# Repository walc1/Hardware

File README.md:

# Hardware
Hardware-Projekte der n-tree

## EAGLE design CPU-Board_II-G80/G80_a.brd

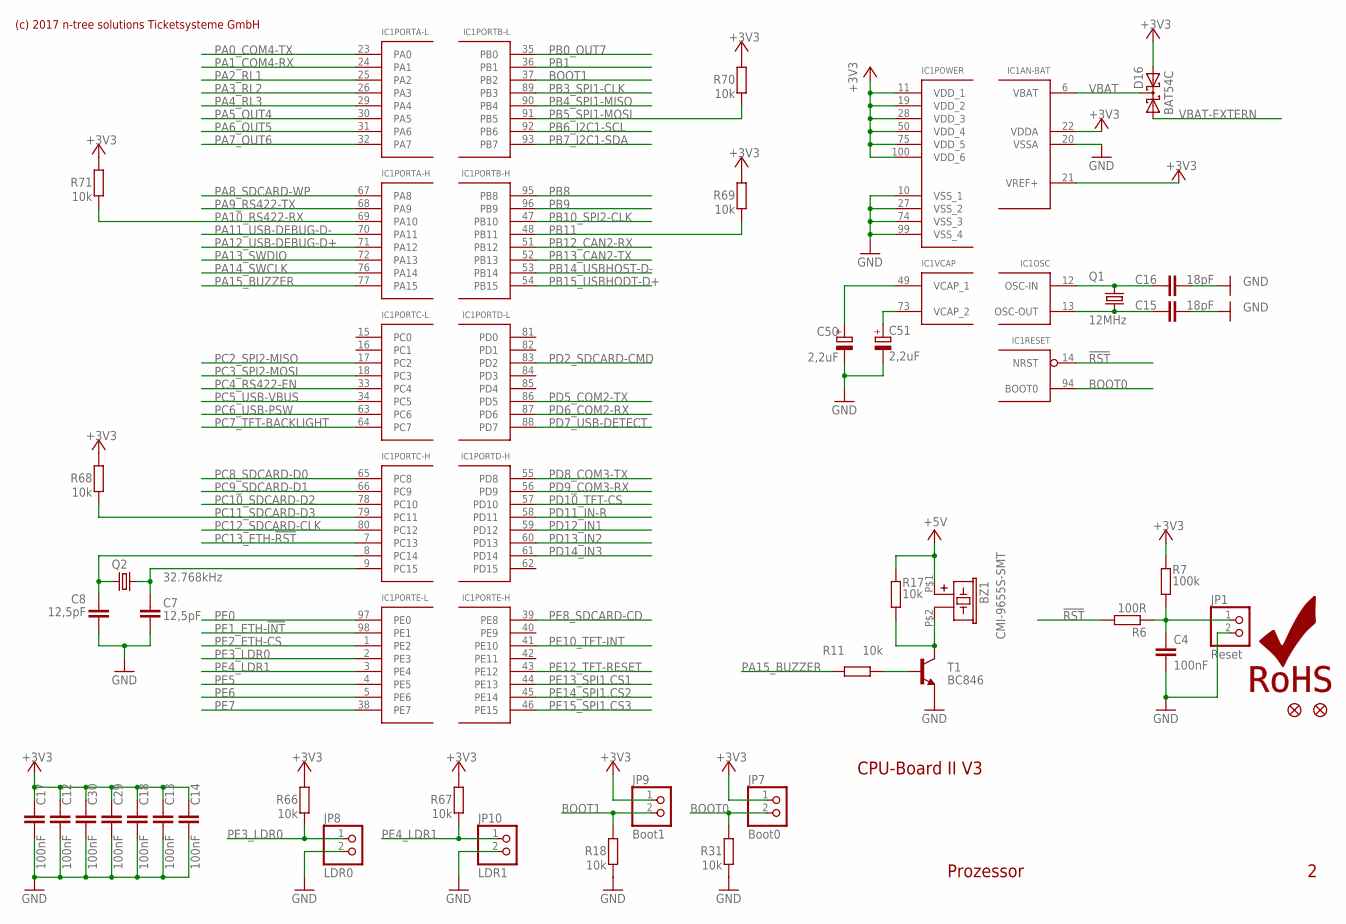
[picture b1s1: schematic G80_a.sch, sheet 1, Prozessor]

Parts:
BZ1: CMI-9655S-SMT; KTG0905CL
C4, C12, C13, C14, C17, C18, C29, C30: 100nF; C0603
C7, C8: 12,5pF; C0603
C15, C16: 18pF; C0603
C50, C51: 2,2uF; CT3216
D16: BAT54C; SOT23
FID1, FID2: FIDUCIAL1X2; FIDUCIAL-1X2
IC1: STM32F107; LQFP100
JP1: Reset; 1X02
JP7: Boot0; 1X02
JP8: LDR0; 1X02
JP9: Boot1; 1X02
JP10: LDR1; 1X02
LOGO1: ROHS_LOGO; ROHS_LOGO_0.18_IN
Q1: 12MHz; CTS406
Q2: 32.768kHz; 3.2X1.5-2-PAD
R6: 100R; R0603
R7: 100k; R0603
R11, R17, R18, R31, R66, R67, R68, R69, R70, R71: 10k; R0603
T1: BC846; SOT23

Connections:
!RST: IC1.14 (NRST), R6.2; also elsewhere on the board
+3V3: C12.1, C13.1, C14.1, C17.1, C18.1, C29.1, C30.1, D16.2 (A2), IC1.11 (VDD_1), IC1.19 (VDD_2), IC1.21 (VREF+), IC1.22 (VDDA), IC1.28 (VDD_3), IC1.50 (VDD_4), IC1.75 (VDD_5), IC1.100 (VDD_6), JP7.1, JP9.1, R7.2, R66.1, R67.1, R68.1, R69.1, R70.1, R71.1; also elsewhere on the board
+5V: BZ1.P$1 (1), R17.1; also elsewhere on the board
BOOT0: IC1.94 (BOOT0), JP7.2, R31.1
BOOT1: IC1.37 (PB2), JP9.2, R18.1
GND: C4.2, C7.2, C8.2, C12.2, C13.2, C14.2, C15.2, C16.2, C17.2, C18.2, C29.2, C30.2, C50.-, C51.-, IC1.10 (VSS_1), IC1.20 (VSSA), IC1.27 (VSS_2), IC1.74 (VSS_3), IC1.99 (VSS_4), JP1.2, JP8.2, JP10.2, R18.2, R31.2, T1.2 (E); also elsewhere on the board
unnamed: C15.1, IC1.13 (OSC-OUT), Q1.1
unnamed: C16.1, IC1.12 (OSC-IN), Q1.3 (2)
unnamed: C7.1, IC1.9 (PC15), Q2.2
unnamed: C8.1, IC1.8 (PC14), Q2.1
unnamed: C51.+, IC1.73 (VCAP_2)
unnamed: BZ1.P$2 (2), R17.2, T1.3 (C)
unnamed: R11.2, T1.1 (B)
unnamed: C4.1, JP1.1, R6.1, R7.1
unnamed: C50.+, IC1.49 (VCAP_1)
PA0_COM4-TX: IC1.23 (PA0); also elsewhere on the board
PA1_COM4-RX: IC1.24 (PA1); also elsewhere on the board
PA2_RL1: IC1.25 (PA2); also elsewhere on the board
PA3_RL2: IC1.26 (PA3); also elsewhere on the board
PA4_RL3: IC1.29 (PA4); also elsewhere on the board
PA5_OUT4: IC1.30 (PA5); also elsewhere on the board
PA6_OUT5: IC1.31 (PA6); also elsewhere on the board
PA7_OUT6: IC1.32 (PA7); also elsewhere on the board
PA8_SDCARD-WP: IC1.67 (PA8)
PA9_RS422-TX: IC1.68 (PA9); also elsewhere on the board
PA10_RS422-RX: IC1.69 (PA10), R71.2; also elsewhere on the board
PA11_USB-DEBUG-D-: IC1.70 (PA11); also elsewhere on the board
PA12_USB-DEBUG-D+: IC1.71 (PA12); also elsewhere on the board
PA13_SWDIO: IC1.72 (PA13); also elsewhere on the board
PA14_SWCLK: IC1.76 (PA14); also elsewhere on the board
PA15_BUZZER: IC1.77 (PA15), R11.1
PB0_OUT7: IC1.35 (PB0); also elsewhere on the board
PB1: IC1.36 (PB1); also elsewhere on the board
PB3_SPI1-CLK: IC1.89 (PB3); also elsewhere on the board
PB4_SPI1-MISO: IC1.90 (PB4); also elsewhere on the board
PB5_SPI1-MOSI: IC1.91 (PB5), R70.2; also elsewhere on the board
PB6_I2C1-SCL: IC1.92 (PB6); also elsewhere on the board
PB7_I2C1-SDA: IC1.93 (PB7); also elsewhere on the board
PB8: IC1.95 (PB8); also elsewhere on the board
PB9: IC1.96 (PB9); also elsewhere on the board
PB10_SPI2-CLK: IC1.47 (PB10); also elsewhere on the board
PB11: IC1.48 (PB11), R69.2; also elsewhere on the board
PB12_CAN2-RX: IC1.51 (PB12); also elsewhere on the board
PB13_CAN2-TX: IC1.52 (PB13); also elsewhere on the board
PB14_USBHOST-D-: IC1.53 (PB14); also elsewhere on the board
PB15_USBHODT-D+: IC1.54 (PB15); also elsewhere on the board
PC2_SPI2-MISO: IC1.17 (PC2); also elsewhere on the board
PC3_SPI2-MOSI: IC1.18 (PC3); also elsewhere on the board
PC4_RS422-EN: IC1.33 (PC4); also elsewhere on the board
PC5_USB-VBUS: IC1.34 (PC5); also elsewhere on the board
PC6_USB-PSW: IC1.63 (PC6); also elsewhere on the board
PC7_TFT-BACKLIGHT: IC1.64 (PC7); also elsewhere on the board
PC8_SDCARD-D0: IC1.65 (PC8); also elsewhere on the board
PC9_SDCARD-D1: IC1.66 (PC9); also elsewhere on the board
PC10_SDCARD-D2: IC1.78 (PC10); also elsewhere on the board
PC11_SDCARD-D3: IC1.79 (PC11), R68.2; also elsewhere on the board
PC12_SDCARD-CLK: IC1.80 (PC12); also elsewhere on the board
PC13_ETH-!RST: IC1.7 (PC13); also elsewhere on the board
PD2_SDCARD-CMD: IC1.83 (PD2); also elsewhere on the board
PD5_COM2-TX: IC1.86 (PD5); also elsewhere on the board
PD6_COM2-RX: IC1.87 (PD6); also elsewhere on the board
PD7_USB-DETECT: IC1.88 (PD7); also elsewhere on the board
PD8_COM3-TX: IC1.55 (PD8); also elsewhere on the board
PD9_COM3-RX: IC1.56 (PD9); also elsewhere on the board
PD10_TFT-CS: IC1.57 (PD10); also elsewhere on the board
PD11_IN-R: IC1.58 (PD11); also elsewhere on the board
PD12_IN1: IC1.59 (PD12); also elsewhere on the board
PD13_IN2: IC1.60 (PD13); also elsewhere on the board
PD14_IN3: IC1.61 (PD14); also elsewhere on the board
PE0: IC1.97 (PE0); also elsewhere on the board
PE1_ETH-!INT: IC1.98 (PE1); also elsewhere on the board
PE2_ETH-CS: IC1.1 (PE2); also elsewhere on the board
PE3_LDR0: IC1.2 (PE3), JP8.1, R66.2
PE4_LDR1: IC1.3 (PE4), JP10.1, R67.2
PE5: IC1.4 (PE5); also elsewhere on the board
PE6: IC1.5 (PE6); also elsewhere on the board
PE7: IC1.38 (PE7); also elsewhere on the board
PE8_SDCARD-CD: IC1.39 (PE8); also elsewhere on the board
PE10_TFT-INT: IC1.41 (PE10); also elsewhere on the board
PE12_TFT-RESET: IC1.43 (PE12); also elsewhere on the board
PE13_SPI1.CS1: IC1.44 (PE13); also elsewhere on the board
PE14_SPI1.CS2: IC1.45 (PE14); also elsewhere on the board
PE15_SPI1.CS3: IC1.46 (PE15); also elsewhere on the board
VBAT: D16.3 (CC), IC1.6 (VBAT)
VBAT-EXTERN: D16.1 (A1); also elsewhere on the board

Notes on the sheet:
CPU-Board II V3
Prozessor
(c) 2017 n-tree solutions Ticketsysteme GmbH

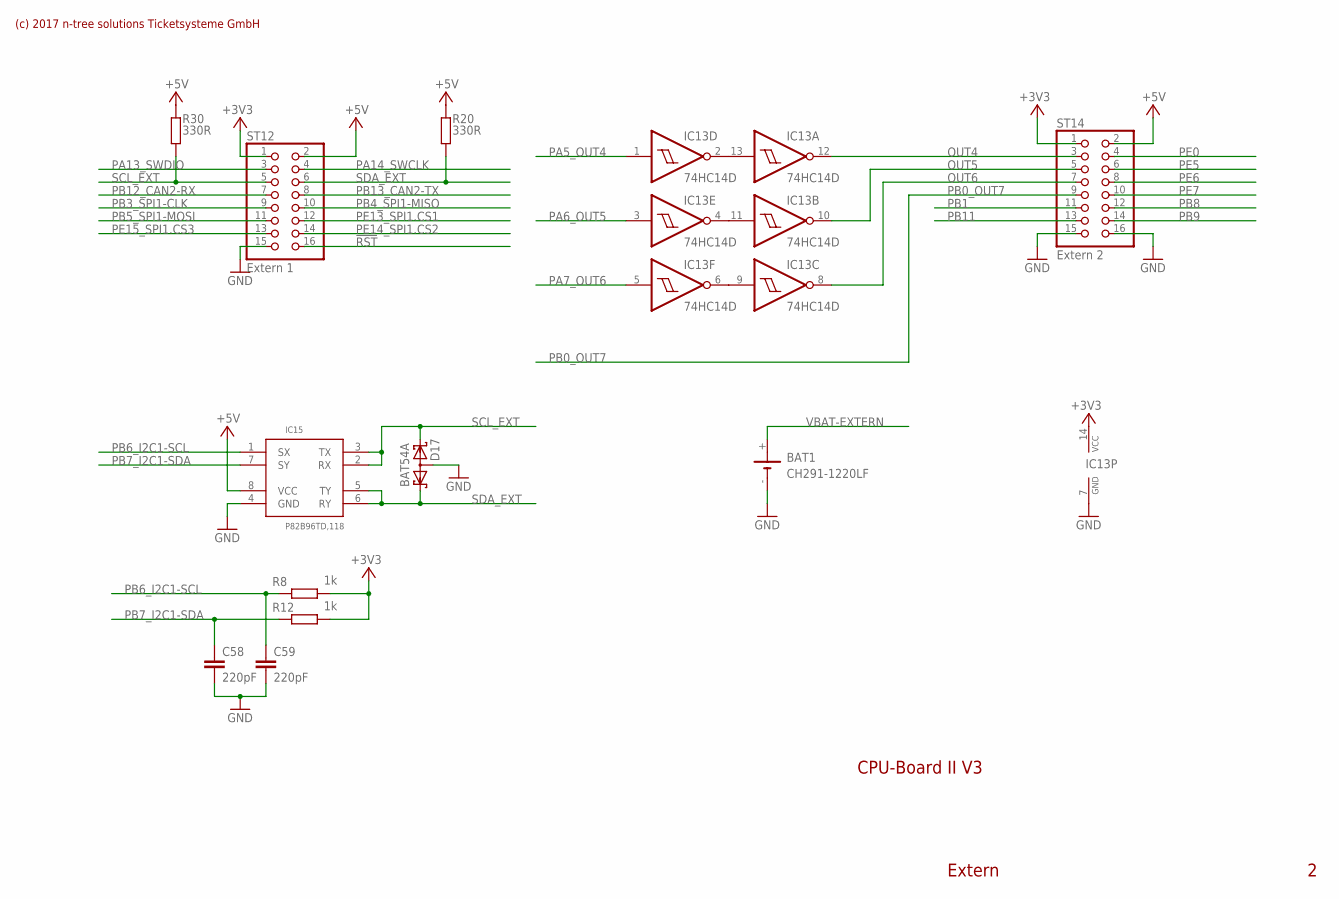
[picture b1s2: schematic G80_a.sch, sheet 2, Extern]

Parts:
BAT1: CH291-1220LF
C58, C59: 220pF; C0603
D17: BAT54A; SOT23
IC13: 74HC14D; SO14
IC15: P82B96TD,118; SO08
R8, R12: 1k; R0603
R20, R30: 330R; R0603
ST12: Extern 1; 2X08
ST14: Extern 2; 2X08

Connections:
!RST: ST12.16; also elsewhere on the board
+3V3: IC13.14 (VCC), R8.2, R12.2, ST12.1, ST14.1; also elsewhere on the board
+5V: IC15.8 (VCC), R20.1, R30.1, ST12.2, ST14.2; also elsewhere on the board
GND: BAT1.-, C58.2, C59.2, D17.3 (AA), IC13.7 (GND), IC15.4 (GND), ST12.15, ST14.15, ST14.16; also elsewhere on the board
unnamed: IC13.2 (O), IC13.13 (I)
unnamed: IC13.4 (O), IC13.11 (I)
unnamed: IC13.6 (O), IC13.9 (I)
OUT4: IC13.12 (O), ST14.3
OUT5: IC13.10 (O), ST14.5
OUT6: IC13.8 (O), ST14.7
PA5_OUT4: IC13.1 (I); also elsewhere on the board
PA6_OUT5: IC13.3 (I); also elsewhere on the board
PA7_OUT6: IC13.5 (I); also elsewhere on the board
PA13_SWDIO: ST12.3; also elsewhere on the board
PA14_SWCLK: ST12.4; also elsewhere on the board
PB0_OUT7: ST14.9; also elsewhere on the board
PB1: ST14.11; also elsewhere on the board
PB3_SPI1-CLK: ST12.9; also elsewhere on the board
PB4_SPI1-MISO: ST12.10; also elsewhere on the board
PB5_SPI1-MOSI: ST12.11; also elsewhere on the board
PB6_I2C1-SCL: C59.1, IC15.1 (SX), R8.1; also elsewhere on the board
PB7_I2C1-SDA: C58.1, IC15.7 (SY), R12.1; also elsewhere on the board
PB8: ST14.12; also elsewhere on the board
PB9: ST14.14; also elsewhere on the board
PB11: ST14.13; also elsewhere on the board
PB12_CAN2-RX: ST12.7; also elsewhere on the board
PB13_CAN2-TX: ST12.8; also elsewhere on the board
PE0: ST14.4; also elsewhere on the board
PE5: ST14.6; also elsewhere on the board
PE6: ST14.8; also elsewhere on the board
PE7: ST14.10; also elsewhere on the board
PE13_SPI1.CS1: ST12.12; also elsewhere on the board
PE14_SPI1.CS2: ST12.14; also elsewhere on the board
PE15_SPI1.CS3: ST12.13; also elsewhere on the board
SCL_EXT: D17.2 (K2), IC15.2 (RX), IC15.3 (TX), R30.2, ST12.5
SDA_EXT: D17.1 (K1), IC15.5 (TY), IC15.6 (RY), R20.2, ST12.6
VBAT-EXTERN: BAT1.+; also elsewhere on the board

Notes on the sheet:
CPU-Board II V3
Extern
(c) 2017 n-tree solutions Ticketsysteme GmbH

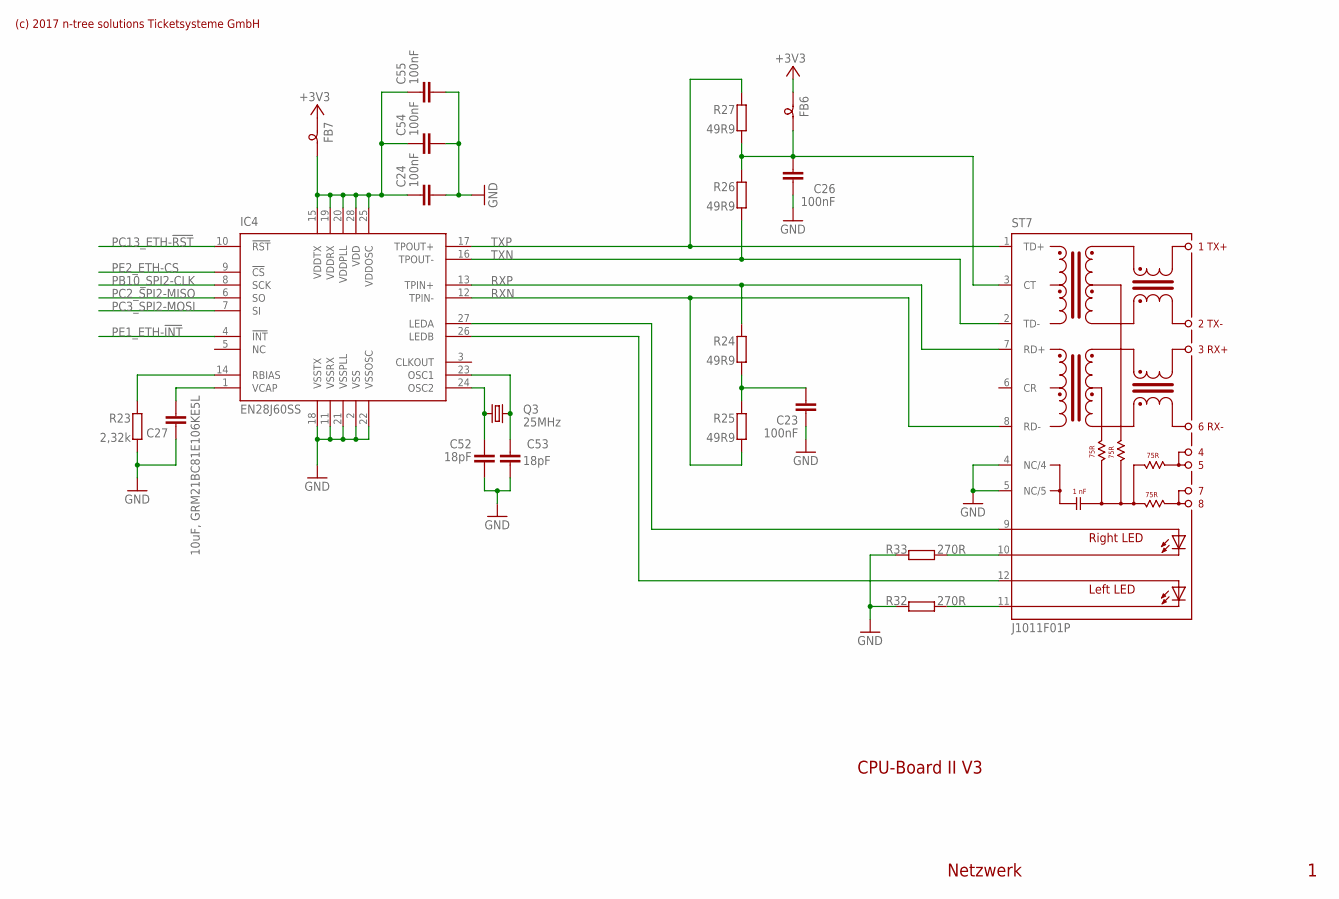
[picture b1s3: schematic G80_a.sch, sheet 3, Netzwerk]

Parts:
C23, C24, C26, C54, C55: 100nF; C0603
C27: 10uF, GRM21BC81E106KE5L; C0805
C52, C53: 18pF; C0603
FB6, FB7: FERITTE-CHIP-BEAD; R805
IC4: EN28J60SS; SSOP28
Q3: 25MHz; CTS406
R23: 2,32k; R0603
R24, R25, R26, R27: 49R9; R0603
R32, R33: 270R; R0603
ST7: J1011F01P; J1

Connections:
+3V3: FB6.1, FB7.1; also elsewhere on the board
GND: C23.2, C24.2, C26.2, C27.2, C52.2, C53.2, C54.2, C55.2, IC4.2 (VSS), IC4.11 (VSSRX), IC4.18 (VSSTX), IC4.21 (VSSPLL), IC4.22 (VSSOSC), R23.1, R32.1, R33.1, ST7.4 (NC/4), ST7.5 (NC/5); also elsewhere on the board
unnamed: R33.2, ST7.10 (C-R)
unnamed: R32.2, ST7.11 (C-L)
unnamed: IC4.27 (LEDA), ST7.9 (A-R)
unnamed: IC4.26 (LEDB), ST7.12 (AL)
unnamed: C24.1, C54.1, C55.1, FB7.2, IC4.15 (VDDTX), IC4.19 (VDDRX), IC4.20 (VDDPLL), IC4.25 (VDDOSC), IC4.28 (VDD)
unnamed: C23.1, R24.1, R25.2
unnamed: C26.1, FB6.2, R26.2, R27.1, ST7.3 (CT)
unnamed: C52.1, IC4.24 (OSC2), Q3.1
unnamed: C53.1, IC4.23 (OSC1), Q3.3 (2)
unnamed: C27.1, IC4.1 (VCAP)
unnamed: IC4.14 (RBIAS), R23.2
PB10_SPI2-CLK: IC4.8 (SCK); also elsewhere on the board
PC2_SPI2-MISO: IC4.6 (SO); also elsewhere on the board
PC3_SPI2-MOSI: IC4.7 (SI); also elsewhere on the board
PC13_ETH-!RST: IC4.10 (!RST); also elsewhere on the board
PE1_ETH-!INT: IC4.4 (!INT); also elsewhere on the board
PE2_ETH-CS: IC4.9 (!CS); also elsewhere on the board
RXN: IC4.12 (TPIN-), R25.1, ST7.8 (RD-)
RXP: IC4.13 (TPIN+), R24.2, ST7.7 (RD+)
TXN: IC4.16 (TPOUT-), R26.1, ST7.2 (TD-)
TXP: IC4.17 (TPOUT+), R27.2, ST7.1 (TD+)

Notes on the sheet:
CPU-Board II V3
Netzwerk
(c) 2017 n-tree solutions Ticketsysteme GmbH

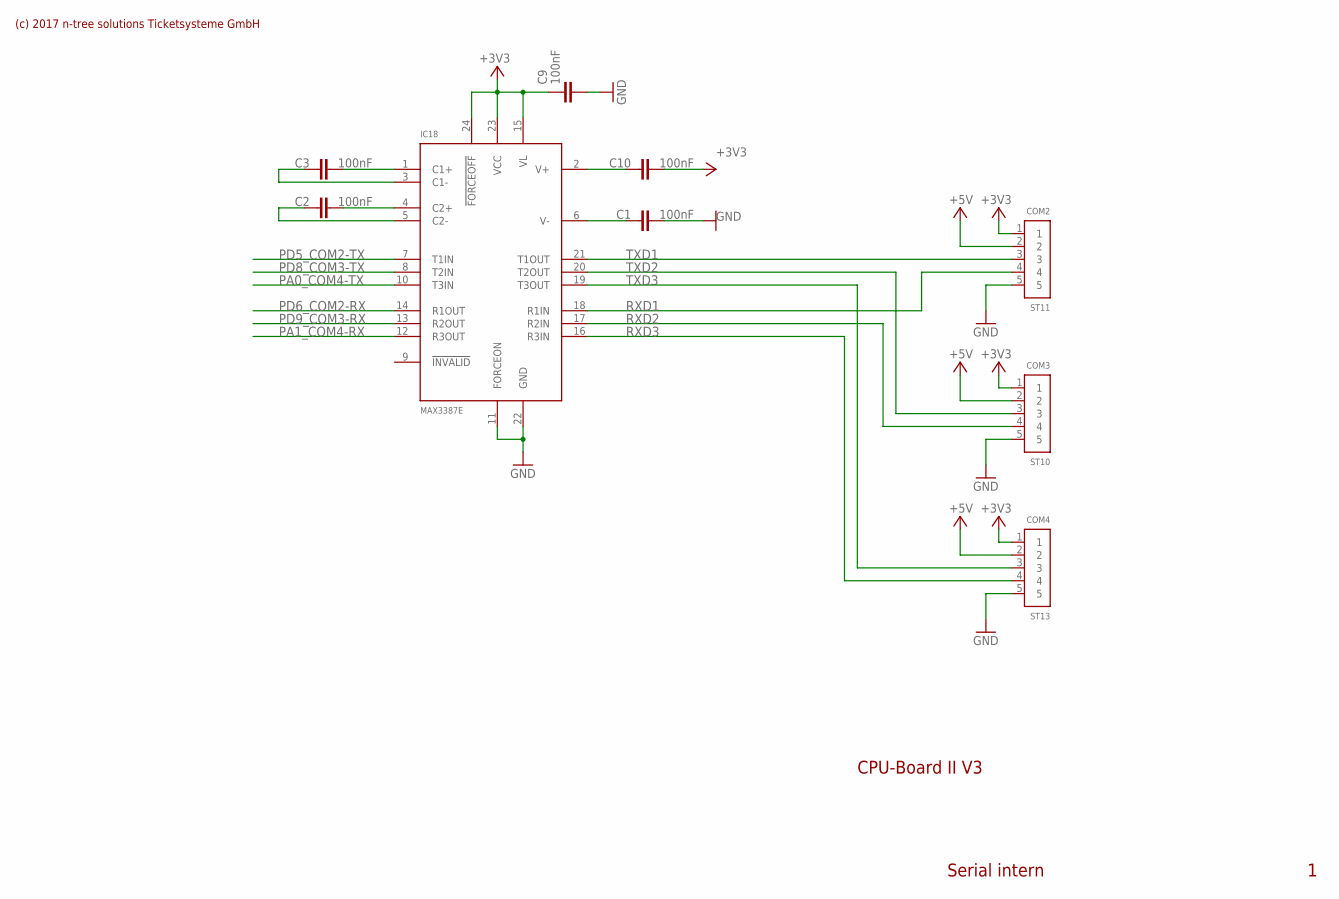
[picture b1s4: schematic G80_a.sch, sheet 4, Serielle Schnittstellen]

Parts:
C1, C2, C3, C9, C10: 100nF; C0603
IC18: MAX3387E; SSOP24
ST10: COM3; JST-EH5
ST11: COM2; JST-EH5
ST13: COM4; JST-EH5

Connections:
+3V3: C9.1, C10.2, IC18.15 (VL), IC18.23 (VCC), IC18.24 (!FORCEOFF), ST10.1, ST11.1, ST13.1; also elsewhere on the board
+5V: ST10.2, ST11.2, ST13.2; also elsewhere on the board
GND: C1.2, C9.2, IC18.11 (FORCEON), IC18.22 (GND), ST10.5, ST11.5, ST13.5; also elsewhere on the board
unnamed: C3.2, IC18.1 (C1+)
unnamed: C3.1, IC18.3 (C1-)
unnamed: C2.2, IC18.4 (C2+)
unnamed: C2.1, IC18.5 (C2-)
unnamed: C10.1, IC18.2 (V+)
unnamed: C1.1, IC18.6 (V-)
PA0_COM4-TX: IC18.10 (T3IN); also elsewhere on the board
PA1_COM4-RX: IC18.12 (R3OUT); also elsewhere on the board
PD5_COM2-TX: IC18.7 (T1IN); also elsewhere on the board
PD6_COM2-RX: IC18.14 (R1OUT); also elsewhere on the board
PD8_COM3-TX: IC18.8 (T2IN); also elsewhere on the board
PD9_COM3-RX: IC18.13 (R2OUT); also elsewhere on the board
RXD1: IC18.18 (R1IN), ST11.4
RXD2: IC18.17 (R2IN), ST10.4
RXD3: IC18.16 (R3IN), ST13.4
TXD1: IC18.21 (T1OUT), ST11.3
TXD2: IC18.20 (T2OUT), ST10.3
TXD3: IC18.19 (T3OUT), ST13.3

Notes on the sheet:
CPU-Board II V3
Serial intern
(c) 2017 n-tree solutions Ticketsysteme GmbH

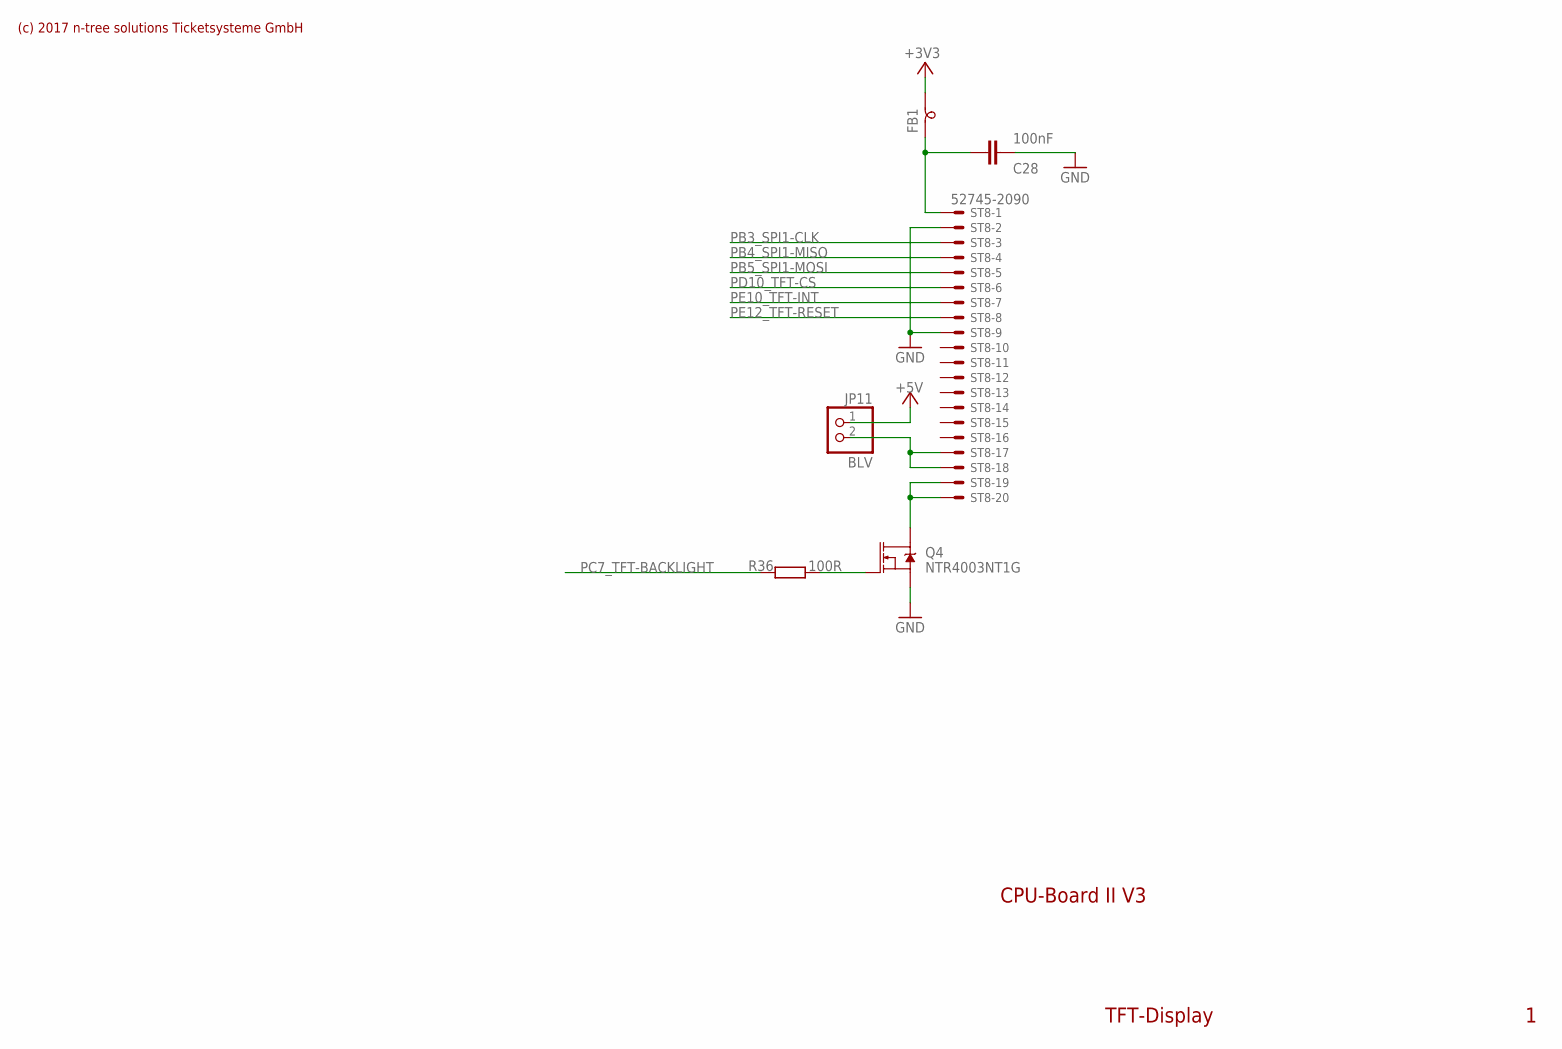
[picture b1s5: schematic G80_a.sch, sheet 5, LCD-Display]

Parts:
C28: 100nF; C0603
FB1: FERITTE-CHIP-BEAD; R805
JP11: BLV; 1X02
Q4: NTR4003NT1G; SOT23-3
R36: 100R; R0603
ST8: 52745-2090

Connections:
+3V3: FB1.2; also elsewhere on the board
+5V: JP11.1; also elsewhere on the board
GND: C28.2, Q4.2 (S), ST8.2, ST8.9; also elsewhere on the board
unnamed: Q4.1 (G), R36.2
unnamed: C28.1, FB1.1, ST8.1
unnamed: Q4.3 (D), ST8.19, ST8.20
unnamed: JP11.2, ST8.17, ST8.18
PB3_SPI1-CLK: ST8.3; also elsewhere on the board
PB4_SPI1-MISO: ST8.4; also elsewhere on the board
PB5_SPI1-MOSI: ST8.5; also elsewhere on the board
PC7_TFT-BACKLIGHT: R36.1; also elsewhere on the board
PD10_TFT-CS: ST8.6; also elsewhere on the board
PE10_TFT-INT: ST8.7; also elsewhere on the board
PE12_TFT-RESET: ST8.8; also elsewhere on the board

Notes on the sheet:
CPU-Board II V3
TFT-Display
(c) 2017 n-tree solutions Ticketsysteme GmbH

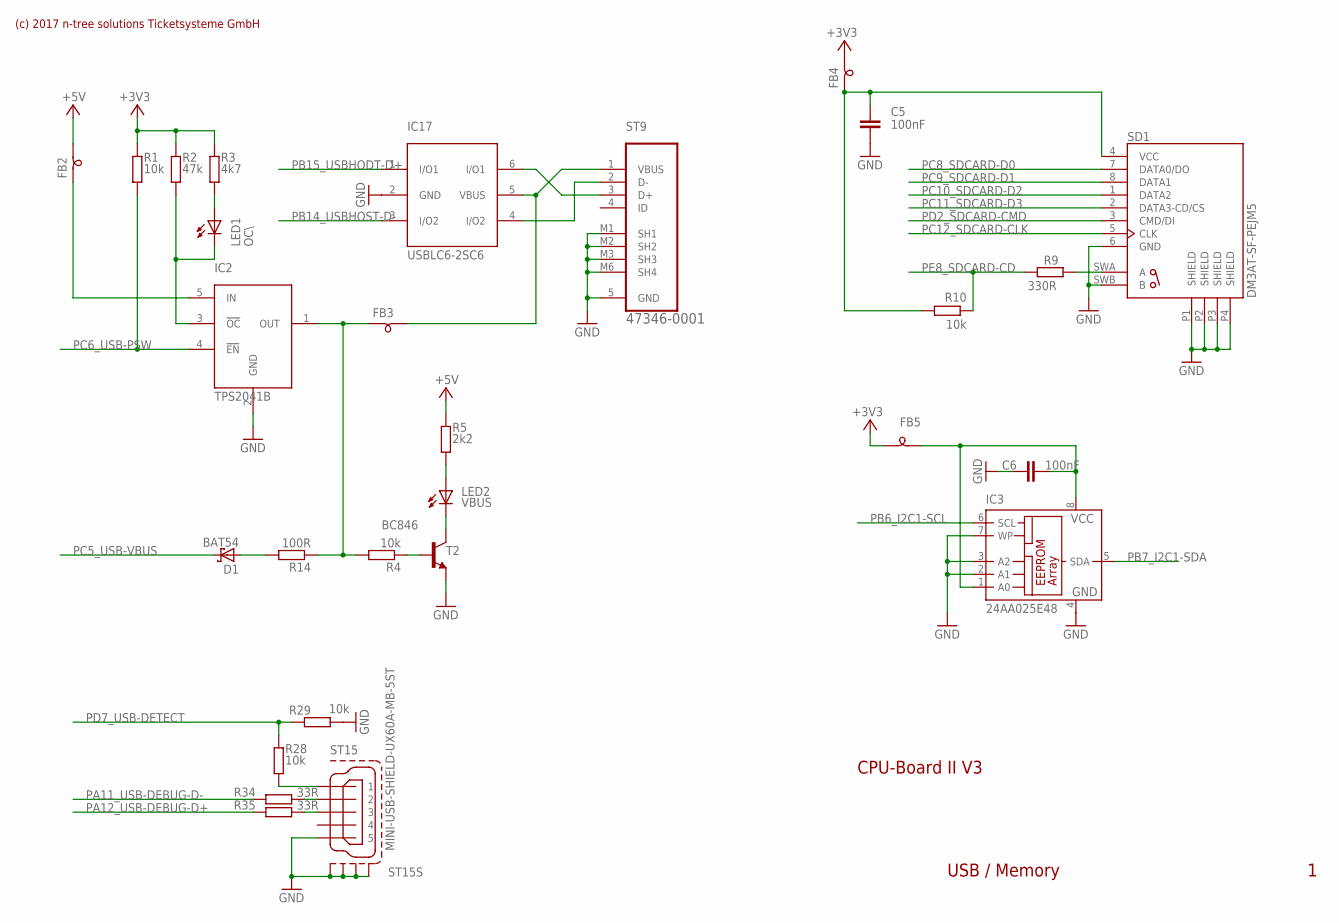
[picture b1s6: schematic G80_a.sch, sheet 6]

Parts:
C5, C6: 100nF; C0603
D1: BAT54; SOT23
FB2, FB3, FB4, FB5: FERITTE-CHIP-BEAD; R805
IC2: TPS2041B; SOT23-5
IC3: 24AA025E48; SO-08M
IC17: USBLC6-2SC6; SO23-6L
LED1: OC\; CHIPLED_0603
LED2: VBUS; CHIPLED_0603
R1, R4, R10, R28, R29: 10k; R0603
R2: 47k; R0603
R3: 4k7; R0603
R5: 2k2; R0603
R9: 330R; R0603
R14: 100R; R0603
R34, R35: 33R; R0603
SD1: DM3AT-SF-PEJM5; HRS_DM3AT-SF-PEJM5
ST9: 47346-0001; MOLEX_47346-0001
ST15: MINI-USB-SHIELD-UX60A-MB-5ST; UX60A-MB-5ST
T2: BC846; SOT23-BEC

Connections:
+3V3: FB4.2, FB5.2, R1.1, R2.1, R3.1; also elsewhere on the board
+5V: FB2.2, R5.1; also elsewhere on the board
GND: C5.2, C6.1, IC2.2 (GND), IC3.2 (A1), IC3.3 (A2), IC3.4 (GND), IC3.7 (WP), IC17.2 (GND), R29.2, SD1.6 (GND), SD1.P1 (SHIELD), SD1.P2 (SHIELD), SD1.P3 (SHIELD), SD1.P4 (SHIELD), SD1.SWB (B), ST9.5 (GND), ST9.M1 (SH1), ST9.M2 (SH2), ST9.M3 (SH3), ST9.M6 (SH4), ST15.5, ST15.M1 (S1), ST15.M2 (S2), ST15.M3 (S3), ST15.M4 (S4), T2.E; also elsewhere on the board
unnamed: LED2.C, T2.C
unnamed: LED1.A, R3.2
unnamed: LED2.A, R5.2
unnamed: R4.1, T2.B
unnamed: FB3.1, IC2.1 (OUT), R4.2, R14.1
unnamed: D1.1 (A), R14.2
unnamed: IC2.3 (!OC), LED1.C, R2.2
unnamed: R9.1, SD1.SWA (A)
unnamed: R28.2, ST15.1
unnamed: R34.1, ST15.2
unnamed: R35.1, ST15.3
unnamed: FB3.2, IC17.5 (VBUS), ST9.1 (VBUS)
unnamed: IC17.6 (I/O1), ST9.3 (D+)
unnamed: FB2.1, IC2.5 (IN)
unnamed: IC17.4 (I/O2), ST9.2 (D-)
unnamed: C5.1, FB4.1, R10.1, SD1.4 (VCC)
unnamed: C6.2, FB5.1, IC3.1 (A0), IC3.8 (VCC)
PA11_USB-DEBUG-D-: R34.2; also elsewhere on the board
PA12_USB-DEBUG-D+: R35.2; also elsewhere on the board
PB6_I2C1-SCL: IC3.6 (SCL); also elsewhere on the board
PB7_I2C1-SDA: IC3.5 (SDA); also elsewhere on the board
PB14_USBHOST-D-: IC17.3 (I/O2); also elsewhere on the board
PB15_USBHODT-D+: IC17.1 (I/O1); also elsewhere on the board
PC5_USB-VBUS: D1.3 (C); also elsewhere on the board
PC6_USB-PSW: IC2.4 (!EN), R1.2; also elsewhere on the board
PC8_SDCARD-D0: SD1.7 (DATA0/DO); also elsewhere on the board
PC9_SDCARD-D1: SD1.8 (DATA1); also elsewhere on the board
PC10_SDCARD-D2: SD1.1 (DATA2); also elsewhere on the board
PC11_SDCARD-D3: SD1.2 (DATA3-CD/CS); also elsewhere on the board
PC12_SDCARD-CLK: SD1.5 (CLK); also elsewhere on the board
PD2_SDCARD-CMD: SD1.3 (CMD/DI); also elsewhere on the board
PD7_USB-DETECT: R28.1, R29.1; also elsewhere on the board
PE8_SDCARD-CD: R9.2, R10.2; also elsewhere on the board

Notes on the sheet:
CPU-Board II V3
USB / Memory
(c) 2017 n-tree solutions Ticketsysteme GmbH

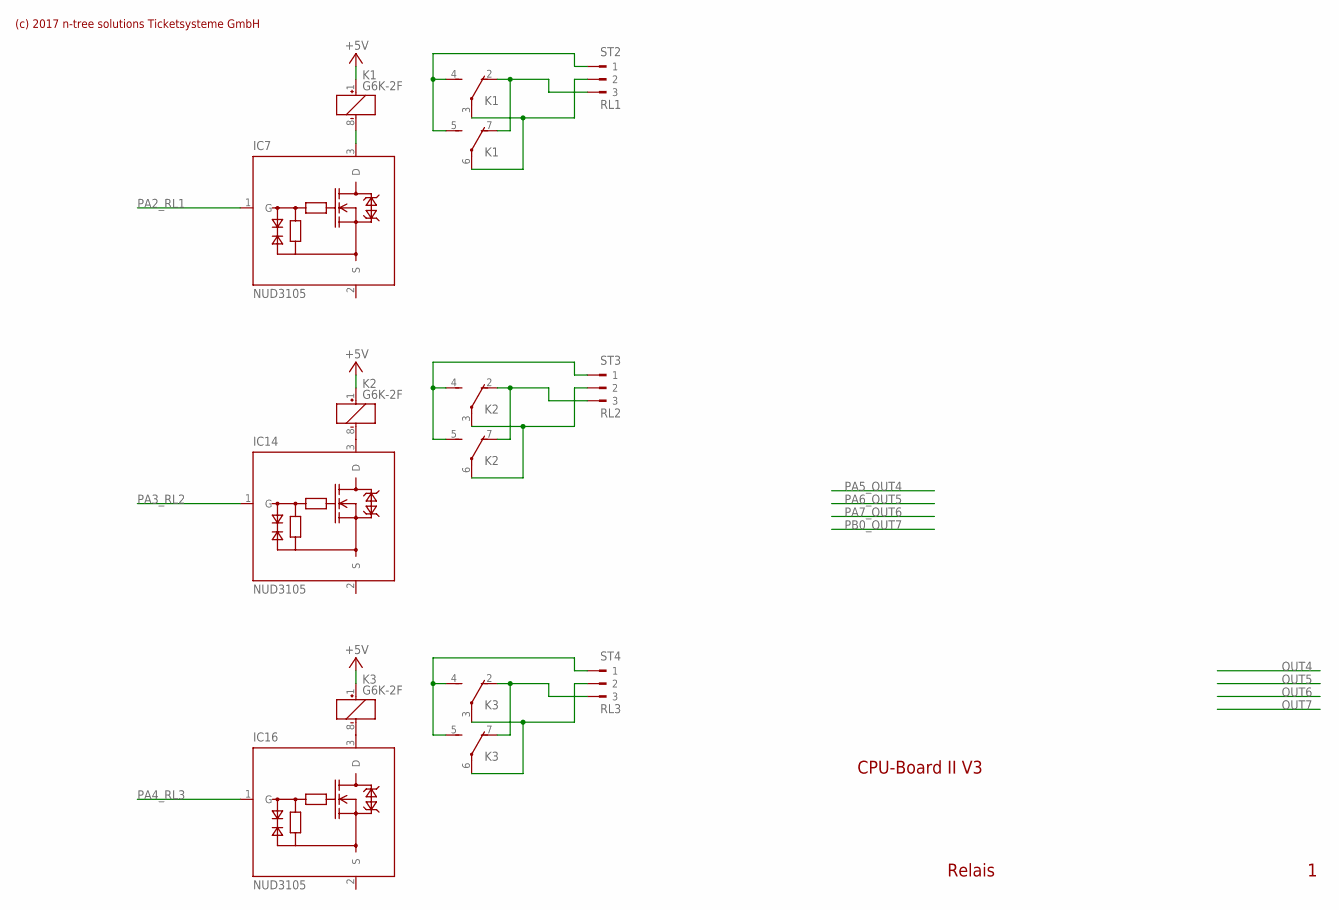
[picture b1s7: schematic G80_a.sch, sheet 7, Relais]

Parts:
IC7, IC14, IC16: NUD3105; SOT23
K1, K2, K3: G6K-2F
ST2: RL1; 180G-3
ST3: RL2; 180G-3
ST4: RL3; 180G-3

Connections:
+5V: K1.1 (+), K2.1 (+), K3.1 (+); also elsewhere on the board
unnamed: K3.4 (S), K3.5 (S), ST4.1
unnamed: K3.2 (O), K3.7 (O), ST4.3
unnamed: K3.3, K3.6, ST4.2
unnamed: K2.4 (S), K2.5 (S), ST3.1
unnamed: K2.2 (O), K2.7 (O), ST3.3
unnamed: K2.3, K2.6, ST3.2
unnamed: K1.4 (S), K1.5 (S), ST2.1
unnamed: K1.2 (O), K1.7 (O), ST2.3
unnamed: K1.3, K1.6, ST2.2
unnamed: IC7.3 (D), K1.8 (-)
unnamed: IC14.3 (D), K2.8 (-)
unnamed: IC16.3 (D), K3.8 (-)
PA2_RL1: IC7.1 (G); also elsewhere on the board
PA3_RL2: IC14.1 (G); also elsewhere on the board
PA4_RL3: IC16.1 (G); also elsewhere on the board

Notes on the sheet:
CPU-Board II V3
(c) 2017 n-tree solutions Ticketsysteme GmbH
Relais

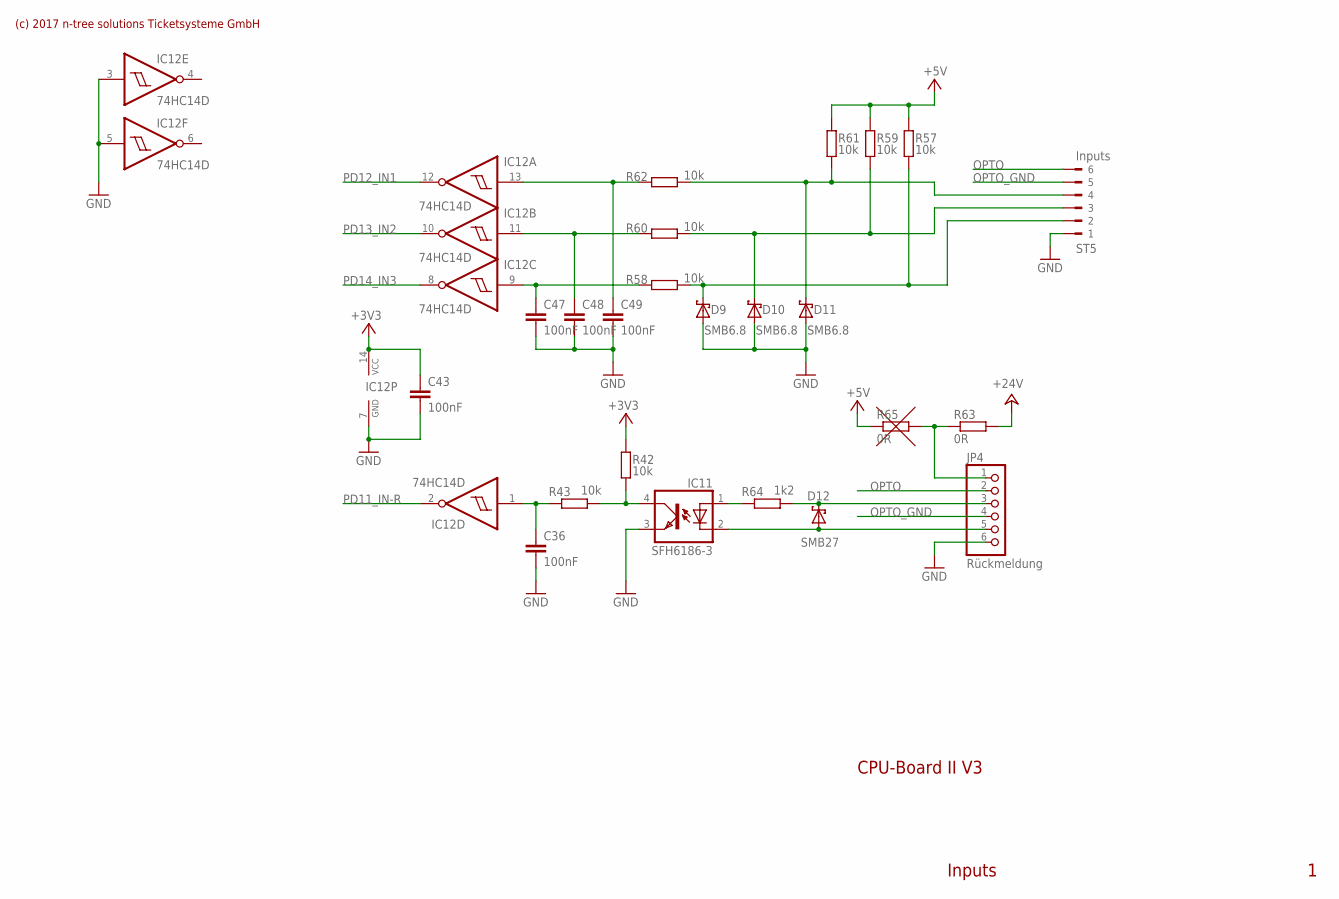
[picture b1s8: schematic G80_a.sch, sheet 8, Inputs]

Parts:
C36, C43, C47, C48, C49: 100nF; C0603
D9, D10, D11: SMB6.8; SMB
D12: SMB27; SMB
IC11: SFH6186-3; SO-6/4
IC12: 74HC14D; SO14
JP4: Rückmeldung; 1X06
R42, R43, R57, R58, R59, R60, R61, R62: 10k; R0603
R63, R65: 0R; R0603
R64: 1k2; R0603
ST5: Inputs; 180G-6

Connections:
+3V3: C43.1, IC12.14 (VCC), R42.2; also elsewhere on the board
+5V: R57.2, R59.2, R61.2, R65.1; also elsewhere on the board
+24V: R63.2; also elsewhere on the board
GND: C36.2, C43.2, C47.2, C48.2, C49.2, D9.A, D10.A, D11.A, IC11.3 (EMIT), IC12.3 (I), IC12.5 (I), IC12.7 (GND), JP4.6, ST5.1; also elsewhere on the board
unnamed: JP4.1, R63.1, R65.2
unnamed: C36.1, IC12.1 (I), R43.1
unnamed: D9.C, R57.1, R58.2, ST5.2
unnamed: D10.C, R59.1, R60.2, ST5.3
unnamed: D11.C, R61.1, R62.2, ST5.4
unnamed: IC11.4 (COL), R42.1, R43.2
unnamed: D12.A, IC11.2 (C), JP4.5
unnamed: D12.C, JP4.3, R64.2
unnamed: IC11.1 (A), R64.1
unnamed: C49.1, IC12.13 (I), R62.1
unnamed: C48.1, IC12.11 (I), R60.1
unnamed: C47.1, IC12.9 (I), R58.1
OPTO: JP4.2, ST5.6
OPTO_GND: JP4.4, ST5.5
PD11_IN-R: IC12.2 (O); also elsewhere on the board
PD12_IN1: IC12.12 (O); also elsewhere on the board
PD13_IN2: IC12.10 (O); also elsewhere on the board
PD14_IN3: IC12.8 (O); also elsewhere on the board

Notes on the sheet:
CPU-Board II V3
(c) 2017 n-tree solutions Ticketsysteme GmbH
Inputs

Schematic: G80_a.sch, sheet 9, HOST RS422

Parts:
C33, C45: 10uF/16V; C/6032-28R
C34, C35, C39, C40, C41, C42, C46: 100nF; C0603
C38: 1uF/16V; A/3216-18R
C44: 10nF/50V; C0603
D3: BZV50C5V6; SOD80C
D4, D5, D6, D8: SMB15A; SMB
D7: BAV99; SOT23
DC1: TME0505S; NME
IC9: TI_SN65HVD3080E
IC10: 74HC14D; SO14
JP2, JP3: RS484Abschluss; 1X02
OK1, OK2, OK3: HCPL0600; SOIC08
R40, R49, R50: 470R; R0603
R41, R47, R48: 1K5; R0603
R51: 10k; R0603
R52, R54, R56: 100R; R0603
R55: 100k; R0603
ST6: HOST; 180G-4

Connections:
+3V3: C35.1, C40.1, C41.1, C42.1, IC10.14 (VCC), OK1.8 (VCC), OK2.2 (A), OK3.2 (A), R41.2; also elsewhere on the board
+5V: C33.+, DC1.2 (+VIN); also elsewhere on the board
GND: C33.-, C35.2, C40.2, C41.2, C42.2, DC1.1 (-VIN), IC10.7 (GND), OK1.5 (GND), R51.1; also elsewhere on the board
GNDIO: C34.2, C38.-, C39.2, C45.-, C46.2, D3.A, D4.2 (A), D5.2 (A), D6.2 (A), D8.2 (A), DC1.3 (-VOUT), IC9.2 (/RE), IC9.5 (GND), OK2.5 (GND), OK3.5 (GND), R52.1
unnamed: IC10.11 (I), IC10.12 (O)
unnamed: IC10.3 (I), IC10.6 (O)
unnamed: OK3.3 (C), R50.2
unnamed: IC10.10 (O), R50.1
unnamed: IC10.1 (I), IC10.8 (O)
unnamed: OK2.3 (C), R49.2
unnamed: IC10.2 (O), R49.1
unnamed: IC9.4 (D), OK2.6 (VO), R47.1
unnamed: IC10.5 (I), OK1.6 (VO), R41.1
unnamed: IC9.1 (R), R40.2
unnamed: JP3.1, R54.2
unnamed: D7.3 (AC), R55.2
unnamed: OK1.3 (C), R40.1
unnamed: IC9.3 (DE), OK3.6 (VO), R48.1
unnamed: C44.1, JP2.1
unnamed: C44.2, R56.2
PA9_RS422-TX: IC10.9 (I); also elsewhere on the board
PA10_RS422-RX: IC10.4 (O); also elsewhere on the board
PC4_RS422-EN: IC10.13 (I), R51.2; also elsewhere on the board
RX+: D6.1 (C), IC9.9 (A), JP2.2, R55.1, ST6.3
RX-: D8.1 (C), IC9.8 (B), R52.2, R56.1, ST6.4
TX+: D4.1 (C), IC9.6 (Y), JP3.2, ST6.1
TX-: D5.1 (C), IC9.7 (Z), R54.1, ST6.2
VCCIO: C34.1, C38.+, C39.1, C45.+, C46.1, D3.C, D7.1 (A), DC1.4 (+VOUT), IC9.10 (VCC), OK1.2 (A), OK2.8 (VCC), OK3.8 (VCC), R47.2, R48.2

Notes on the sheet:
CPU-Board II V3
(c) 2017 n-tree solutions Ticketsysteme GmbH
RS422 Host

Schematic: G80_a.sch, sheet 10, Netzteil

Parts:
B1: 2KBP02M; 2KBP
C11: 10uF; C/6032-28R
C19: 220uF/35V; 150CLZ-0810
C20, C21, C57: 100nF; C0603
C22, C25: 100uF/16V lowESR; D/7343-31R
C31: 4,7µF lowESR 50V; D/7343-31R
C32: 10nF/100V; C0603
C37: 1000uF/50V; E5-13
C56: 0,33uF/100V; C1206
D2: MBRD650CT; DPACK_3
F1: 2A; RXEF025-2
IC5: MC33269DT3.3; D-PAK
IC6: 7824DT; TO252
IC8: LM2267TJ-ADJ; TO263-7
JP5, JP6: AC/DC; 1X02
L1: 15µH 5A; WE-PD_L/XL/XXL
L2: RN112-02/02; RN112
LCL1, LCL2: 6A,10N; T-FILTERSIL
LED3: LED_+3V3; CHIPLED_0603
LED4: LED +5V; CHIPLED_0603
LED5: LED +24V; CHIPLED_0603
R13, R16: 470R; R0603
R15: 220R; R0603
R19, R21, R22: 0R; R1206
R44: 2k2; R0603
R45: 10k; R0603
R46: 820; R0603
R53: S10K30; S10K17
ST1: Power; 180G-2
ST16: Lüfter; JST-EH2

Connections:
0V: B1.-, C25.-, C31.-, C37.-, C56.2, C57.2, D2.1, D2.3, IC6.3 (GND), IC8.4 (GND), IC8.8 (GND), JP6.1, LCL1.2 (GND), LCL2.2 (GND), LED5.C, R19.2, R21.2, R22.2, R45.1, R46.1, ST16.2
+3V3: C11.+, C21.1, IC5.2 (OUT), R15.2; also elsewhere on the board
+5V: C19.+, C20.1, C22.+, IC5.3 (IN), LCL1.3 (2), R16.2; also elsewhere on the board
+24V: C57.1, IC6.2 (VO), R13.2, ST16.1; also elsewhere on the board
GND: C11.-, C19.-, C20.2, C21.2, C22.-, IC5.1 (GND), LED3.C, LED4.C, R19.1, R21.1, R22.1; also elsewhere on the board
unnamed: F1.IN, ST1.1
unnamed: L2.3, R53.2, ST1.2
unnamed: B1.AC1, JP5.1, L2.2
unnamed: B1.+, C37.+, JP5.2, LCL2.1
unnamed: LED4.A, R16.1
unnamed: B1.AC2, JP6.2, L2.4
unnamed: LED3.A, R15.1
unnamed: LED5.A, R13.1
unnamed: F1.OUT, L2.1, R53.1
unnamed: C32.1, IC8.3 (BOOT)
unnamed: C32.2, D2.4, IC8.1 (SW), L1.2 (1)
unnamed: IC8.6 (FB), R44.1, R45.2, R46.2
unnamed: C25.+, L1.1 (2), LCL1.1, R44.2
VCC: C31.+, C56.1, IC6.1 (VI), IC8.2 (VIN), LCL2.3 (2)

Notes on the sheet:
CPU-Board II V3
(c) 2017 n-tree solutions Ticketsysteme GmbH
Netzteil

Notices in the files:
parts and their libraries:
ntree: Copyright (c) 2000 - 2004 n-tree solutions Ticketsysteme GmbH
PatternAgents-ProtoPads: License : http://creativecommons.org/licenses/by-sa/4.0
(Creative Commons 4.0)
SparkFun-Aesthetics: Licensing: Creative Commons ShareAlike 4.0 International - https://creativecommons.org/licenses/by-sa/4.0
